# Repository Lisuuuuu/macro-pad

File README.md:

# macro-pad
A 4 key macro pad with a rotary encoder and a 0.91" inch oled display

Parts used
----------------------------------------------------------------------------------------------------------------------------------------------------------------------|
| 4x kalih switches  : [switches](https://www.kailh.net/collections/box-switches)                                                                                      | 
| 0.91" inch display : [ Display (amazon)](https://www.amazon.pl/gp/product/B079H2C7WH/ref=ox_sc_act_title_1?smid=A1X7QLRQH87QA3&th=1)                                 |
| EC11 Rotary encoder : [EC11](https://www.amazon.pl/gp/product/B09L7QZZ46/ref=ox_sc_act_title_2?smid=A1KSSF1FWE30G9&psc=1)                                            |
| Raspberry Pi Pico  : [Pi pico](https://www.amazon.com/Raspberry-Pi-Pico/dp/B09KVB8LVR/ref=sr_1_2?dib=eyJ2IjoiMSJ9.he0hzmPd1R2DUnSic2bLdHwpTWu4B6k9C6XNm2bt5Nj4_GWAW5r1zhymE1rqSslhTA_7gtMVLh4yWN6brvdUpnpV5XfoH_XSInz7c5B_IZX0EKLfBBHU_MUNnIHL09PgO1CbEgPLseYNLUzW1a4e1HOyNWKhCz_9E3mUIcE62BW4L7rclOY81CG-avYaMCtW8WDKWN-6lggS22YyXZ_ohpoN7oBPfCfiCM2xFXxXawc.VASJc_L7OEPPa6OM42D4gxKydxQh0wuUYZEf0KWRpBA&dib_tag=se&keywords=raspberry+pi+pico&qid=1758178393&sr=8-2)          |

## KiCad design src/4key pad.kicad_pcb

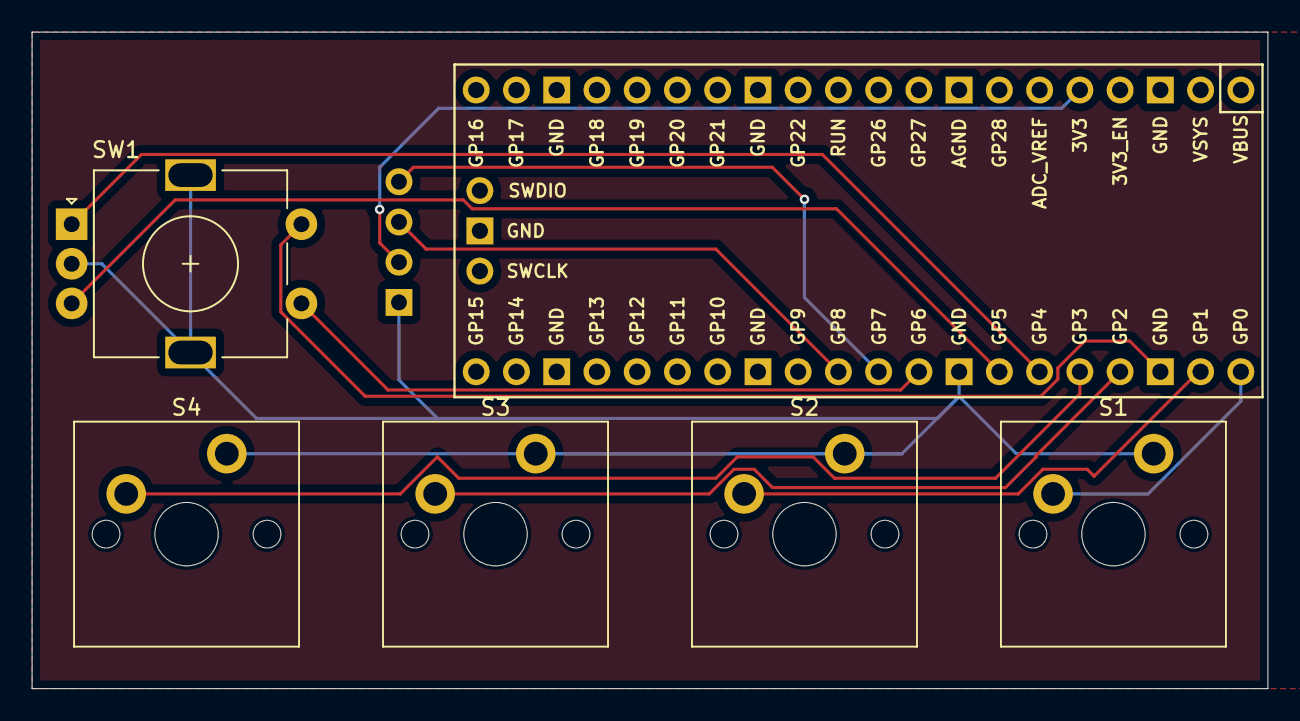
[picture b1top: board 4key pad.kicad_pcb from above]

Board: 2 copper layers, 78.0 x 41.4 mm, 7 parts (1 on the bottom side), 12 nets.

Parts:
J1: OLED_128x32
S1, S2, S3, S4: Keyswitch; MX_PCB_1.00u
SW1: RotaryEncoder_Switch_MP; RotaryEncoder_Alps_EC11E-Switch_Vertical_H20mm
U2: Raspberry_Pi_Pico

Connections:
GND: J1.1 (GND), S1.2, S2.2, S3.2, S4.2, SW1.C, SW1.MP, U2.8 (GND)
VCC: J1.2 (VCC), U2.36 (3V3)
rsw1: SW1.S1, U2.9 (GPIO6)
rsw2: SW1.S2, U2.3 (GND)
scl: J1.3 (SCL), U2.11 (GPIO8)
sda: J1.4 (SDA), U2.10 (GPIO7)
sw1: S1.1, U2.1 (GPIO0)
sw2: S2.1, U2.2 (GPIO1)
sw3: S3.1, U2.4 (GPIO2)
sw4: S4.1, U2.5 (GPIO3)
swa: SW1.A, U2.6 (GPIO4)
swb: SW1.B, U2.7 (GPIO5)

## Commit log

2025-09-10 Create Journal
2025-09-13 Update Journal
2025-09-19 Smth
